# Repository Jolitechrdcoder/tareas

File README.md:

# tareas
tareas electiva mecatronica
# Jorge Luis Martinez Suarez - Portfolio

## Overview
Welcome to my GitHub repository! I'm Jorge Luis Martinez Suarez, a passionate programmer with expertise in various programming languages and technologies. This README.md file provides an overview of my background, skills, and projects. Feel free to explore and discover my work.

## About Me
- Name: Jorge Luis Martinez Suarez
- Matricula: 2018-6244
- Education: Technologist in Mechatronics
- Location: Dominican Republic

## Skills
I have experience and proficiency in the following programming languages and technologies:

- C
- Python
- C++
- HTML
- CSS
- Verilog
- GCodes

## Academic Background
- Technologist in Mechatronics: I have a solid foundation in mechatronics, which combines mechanical, electronic, and computer engineering principles to develop innovative systems and machines.

## Additional Courses
In addition to my formal education, I have completed several courses related to computer repair, electronics, and inverter repairs. These courses include:
- Computer Repair
- Basic Electronics
- Advanced Electronics
- Inverter Repairs
- Electronic Trading Funds (ETF)

## Projects
Below are some notable projects I have worked on. You can find more details and code in the respective repositories:

1. Project Name: level water tanks
   - Description: sistema de monitoreo 
   - Technologies: c++
   - GitHub Repository: https://github.com/Jolitechrdcoder/PROYECTO-ELEC-INDUSTRIAL

2. Project Name: Xor
   - Description: personal assistant
   - Technologies: python and c++
   - GitHub Repository: https://github.com/Jolitechrdcoder/proyectos

## Contact Information
Feel free to reach out to me via the following channels:

- Email: mecatronicosrd@gmail.com

Thank you for visiting my GitHub repository! I look forward to collaborating on exciting projects and exploring new opportunities in the field of programming and mechatronics.

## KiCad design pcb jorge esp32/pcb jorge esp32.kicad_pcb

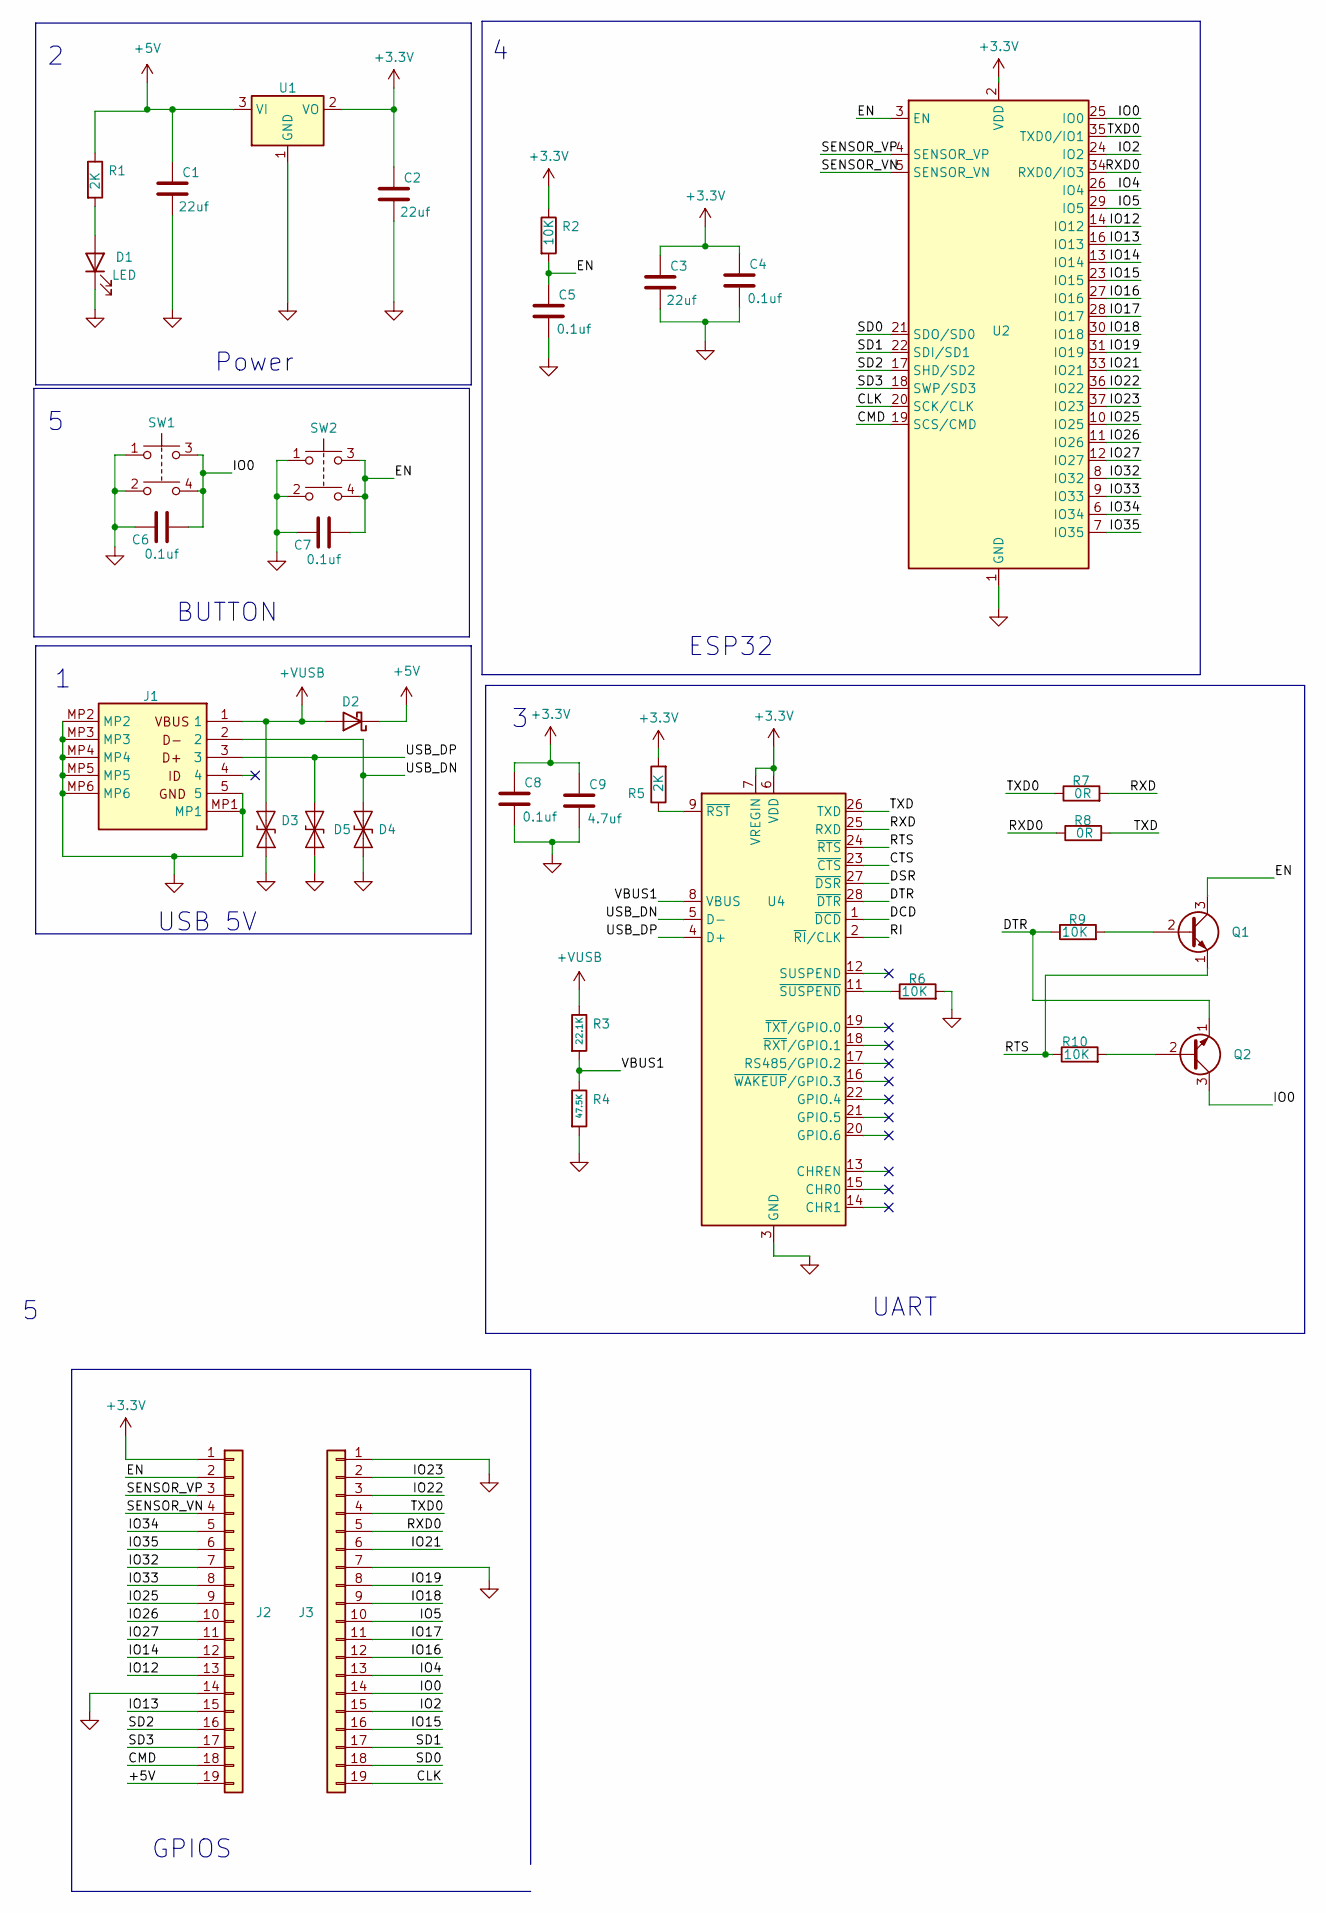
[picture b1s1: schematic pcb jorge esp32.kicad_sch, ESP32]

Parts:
C1, C2, C3: 22uf; C_0603_1608Metric_Pad1.08x0.95mm_HandSolder
C4, C5, C6, C7, C8: 0.1uf; C_0402_1005Metric_Pad0.74x0.62mm_HandSolder
C9: 4.7uf; C_0402_1005Metric_Pad0.74x0.62mm_HandSolder
D1: LED; LED_0603_1608Metric_Pad1.05x0.95mm_HandSolder
D2: D_Schottky; D_SOD-323_HandSoldering
D3, D4, D5: ESD9B3.3ST5G; D_SOD-523
J1: 10118192-0002LF; miniUSB_10118192-0002LF; Mouser Part Number 649-10118192-0002LF
J2, J3: Conn_01x19; PinHeader_1x19_P2.54mm_Vertical
Q1, Q2: S8050; SOT-23-3
R1, R5: 2K; R_0402_1005Metric_Pad0.72x0.64mm_HandSolder
R2, R6, R9, R10: 10K; R_0402_1005Metric_Pad0.72x0.64mm_HandSolder
R3: 22.1K; R_0402_1005Metric_Pad0.72x0.64mm_HandSolder
R4: 47.5K; R_0402_1005Metric_Pad0.72x0.64mm_HandSolder
R7, R8: 0R; R_0402_1005Metric_Pad0.72x0.64mm_HandSolder
SW1, SW2: SW_Push_Dual; KMT021NGJLHS
U1: AMS1117-3.3; SOT-223-3_TabPin2
U2: ESP32-WROOM-32
U4: CP2102N-Axx-xQFN28; QFN50P500X500X80-29N-D

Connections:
+3.3V: C2.1, C3.1, C4.1, C8.1, C9.1, J2.1, R2.1, R5.2, U1.2 (VO), U2.2 (VDD), U4.6 (VDD), U4.7 (VREGIN)
+5V: C1.1, D2.1 (K), J2.19, R1.1, U1.3 (VI)
+VUSB: D2.2 (A), D3.2 (A2), J1.1, R3.1
/CLK: J3.19, U2.20 (SCK/CLK)
/CMD: J2.18, U2.19 (SCS/CMD)
/CTS: U4.23 (~CTS)
/DCD: U4.1 (~DCD)
/DSR: U4.27 (~DSR)
/DTR: Q2.1 (E), R9.1, U4.28 (~DTR)
/EN: C5.1, C7.1, J2.2, Q1.3 (C), R2.2, SW2.3, SW2.4, U2.3 (EN)
/IO0: C6.1, J3.14, Q2.3 (C), SW1.3, SW1.4, U2.25 (IO0)
/IO2: J3.15, U2.24 (IO2)
/IO4: J3.13, U2.26 (IO4)
/IO5: J3.10, U2.29 (IO5)
/IO12: J2.13, U2.14 (IO12)
/IO13: J2.15, U2.16 (IO13)
/IO14: J2.12, U2.13 (IO14)
/IO15: J3.16, U2.23 (IO15)
/IO16: J3.12, U2.27 (IO16)
/IO17: J3.11, U2.28 (IO17)
/IO18: J3.9, U2.30 (IO18)
/IO19: J3.8, U2.31 (IO19)
/IO21: J3.6, U2.33 (IO21)
/IO22: J3.3, U2.36 (IO22)
/IO23: J3.2, U2.37 (IO23)
/IO25: J2.9, U2.10 (IO25)
/IO26: J2.10, U2.11 (IO26)
/IO27: J2.11, U2.12 (IO27)
/IO32: J2.7, U2.8 (IO32)
/IO33: J2.8, U2.9 (IO33)
/IO34: J2.5, U2.6 (IO34)
/IO35: J2.6, U2.7 (IO35)
/RI: U4.2 (~RI/CLK)
/RTS: Q1.1 (E), R10.1, U4.24 (~RTS)
/RXD: R7.2, U4.25 (RXD)
/RXD0: J3.5, R8.1, U2.34 (RXD0/IO3)
/SD0: J3.18, U2.21 (SDO/SD0)
/SD1: J3.17, U2.22 (SDI/SD1)
/SD2: J2.16, U2.17 (SHD/SD2)
/SD3: J2.17, U2.18 (SWP/SD3)
/SENSOR_VN: J2.4, U2.5 (SENSOR_VN)
/SENSOR_VP: J2.3, U2.4 (SENSOR_VP)
/TXD: R8.2, U4.26 (TXD)
/TXD0: J3.4, R7.1, U2.35 (TXD0/IO1)
/USB_DN: D4.2 (A2), J1.2, U4.5 (D-)
/USB_DP: D5.2 (A2), J1.3, U4.4 (D+)
/VBUS1: R3.2, R4.1, U4.8 (VBUS)
GND: C1.2, C2.2, C3.2, C4.2, C5.2, C6.2, C7.2, C8.2, C9.2, D1.1 (K), D3.1 (A1), D4.1 (A1), D5.1 (A1), J1.5, J1.MP1, J1.MP2, J1.MP3, J1.MP4, J1.MP5, J1.MP6, J2.14, J3.1, J3.7, R4.2, R6.2, SW1.1, SW1.2, SW2.1, SW2.2, U1.1 (GND), U2.1 (GND), U2.15 (GND), U2.38 (GND), U2.39 (GND), U4.3 (GND), U4.29 (GND)
unnamed: D1.2 (A), R1.2
unnamed: Q1.2 (B), R9.2
unnamed: Q2.2 (B), R10.2
unnamed: R5.1, U4.9 (~RST)
unnamed: R6.1, U4.11 (~SUSPEND)

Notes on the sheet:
ESP32
BUTTON
Power
USB 5V
GPIOS
UART

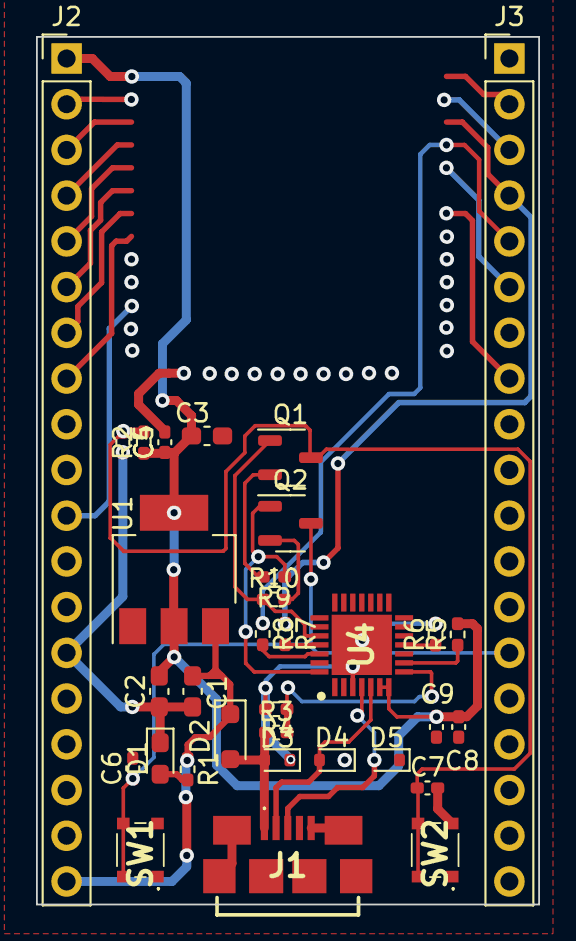
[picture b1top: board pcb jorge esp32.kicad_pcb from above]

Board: 4 copper layers, 27.9 x 48.2 mm, 33 parts (0 on the bottom side), 20 nets.

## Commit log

2023-05-26 README.md
2023-06-09 Create fp-info-cache
